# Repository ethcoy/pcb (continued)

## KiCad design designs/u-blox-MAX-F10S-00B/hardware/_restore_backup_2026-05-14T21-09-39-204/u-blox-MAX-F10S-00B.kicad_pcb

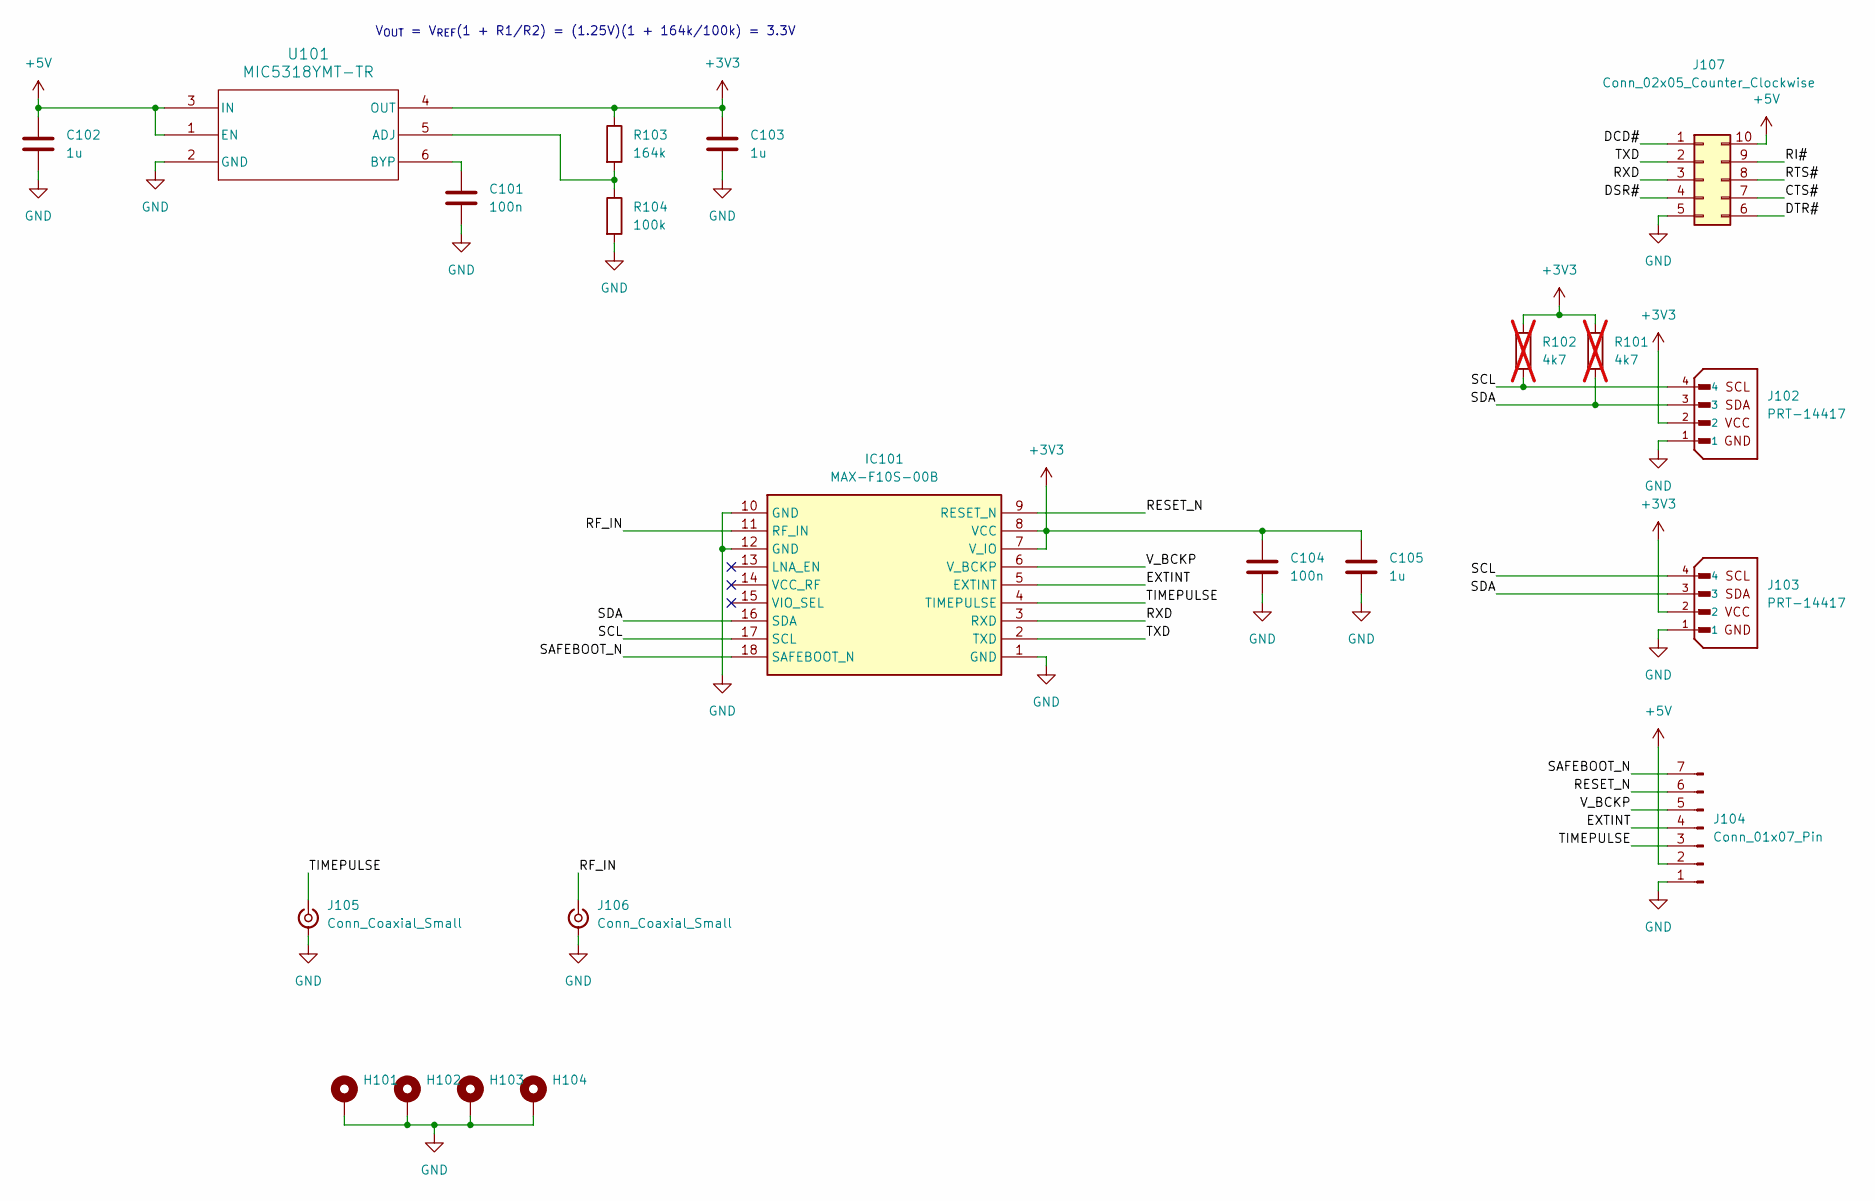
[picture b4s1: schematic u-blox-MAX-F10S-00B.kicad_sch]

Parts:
C101, C104: 100n; C_0402_1005Metric
C102, C103, C105: 1u; C_0402_1005Metric
H101, H102, H103, H104: MountingHole_Pad; MountingHole_2.2mm_M2_Pad_Via
IC101: MAX-F10S-00B; MAXF10S00B; Mouser Part Number 377-MAX-F10S-00B
J102, J103: PRT-14417; PARTREV NA
J104: Conn_01x07_Pin; PinHeader_1x07_P2.54mm_Vertical
J105, J106: Conn_Coaxial_Small; SMA_Amphenol_132289_EdgeMount
J107: Conn_02x05_Counter_Clockwise; PinHeader_2x05_P2.54mm_Vertical_SMD
R101, R102: 4k7; R_0402_1005Metric; not fitted
R103: 164k; R_0402_1005Metric
R104: 100k; R_0402_1005Metric
U101: MIC5318YMT-TR

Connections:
+3V3: C103.1, C104.1, C105.1, IC101.7 (V_IO), IC101.8 (VCC), J102.2, J103.2, R101.1, R102.1, R103.1, U101.4 (OUT)
+5V: C102.1, J104.2, J107.10, U101.1 (EN), U101.3 (IN)
/CTS#: J107.7
/DCD#: J107.1
/DSR#: J107.4
/DTR#: J107.6
/EXTINT: IC101.5 (EXTINT), J104.4
/RESET_N: IC101.9 (RESET_N), J104.6
/RF_IN: IC101.11 (RF_IN), J106.1 (In)
/RI#: J107.9
/RTS#: J107.8
/RXD: IC101.3 (RXD), J107.3
/SAFEBOOT_N: IC101.18 (SAFEBOOT_N), J104.7
/SCL: IC101.17 (SCL), J102.4, J103.4, R102.2
/SDA: IC101.16 (SDA), J102.3, J103.3, R101.2
/TIMEPULSE: IC101.4 (TIMEPULSE), J104.3, J105.1 (In)
/TXD: IC101.2 (TXD), J107.2
/V_BCKP: IC101.6 (V_BCKP), J104.5
GND: C101.2, C102.2, C103.2, C104.2, C105.2, H101.1 (1_1), H102.1 (1_1), H103.1 (1_1), H104.1 (1_1), IC101.1 (GND), IC101.10 (GND), IC101.12 (GND), J102.1, J103.1, J104.1, J105.2 (Ext), J106.2 (Ext), J107.5, R104.2, U101.2 (GND)
unnamed: R103.2, R104.1, U101.5 (ADJ)
unnamed: C101.1, U101.6 (BYP)

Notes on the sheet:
V_{OUT} = V_{REF}(1 + R1/R2) = (1.25V)(1 + 164k/100k) = 3.3V

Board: 4 copper layers, 21 parts (0 on the bottom side), 15 nets, no tracks yet.

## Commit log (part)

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2026-05-13 initial push
2026-05-13 more stuff
2026-05-14 schematic done
2026-05-15 need to check pad to pad clearance of jlcpcb
2026-05-16 pcb done?
2026-05-16 ftdi
2026-05-17 switched to m3 holes
